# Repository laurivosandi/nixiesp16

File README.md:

# NixiESP16

Yet another Nixie clock project!

Some highlights:

* HV5530, HV5522 or similar driven IN-16 tubes
* CD4504B for 3.3V to 12V level shifting
* ESP8266 for time synchronization
* LM1117-3.3V for logic power supply
* No step up converter on-board, pin headers for connecting third party power supply
  <a href="http://www.ebay.com/itm/DC-5V-12V-to-170V-DC-High-Voltage-NIXIE-Power-Supply-Module-PSU-NIXIE-TUBE-ERA-/322511957768?hash=item4b1735ef08">third party power supply</a>
* HV5530 symbol created using
  <a href="http://kicad.rohrbacher.net/quicklib.php">Quick KICAD Library Component Builder</a>

Some KiCad screenshots:

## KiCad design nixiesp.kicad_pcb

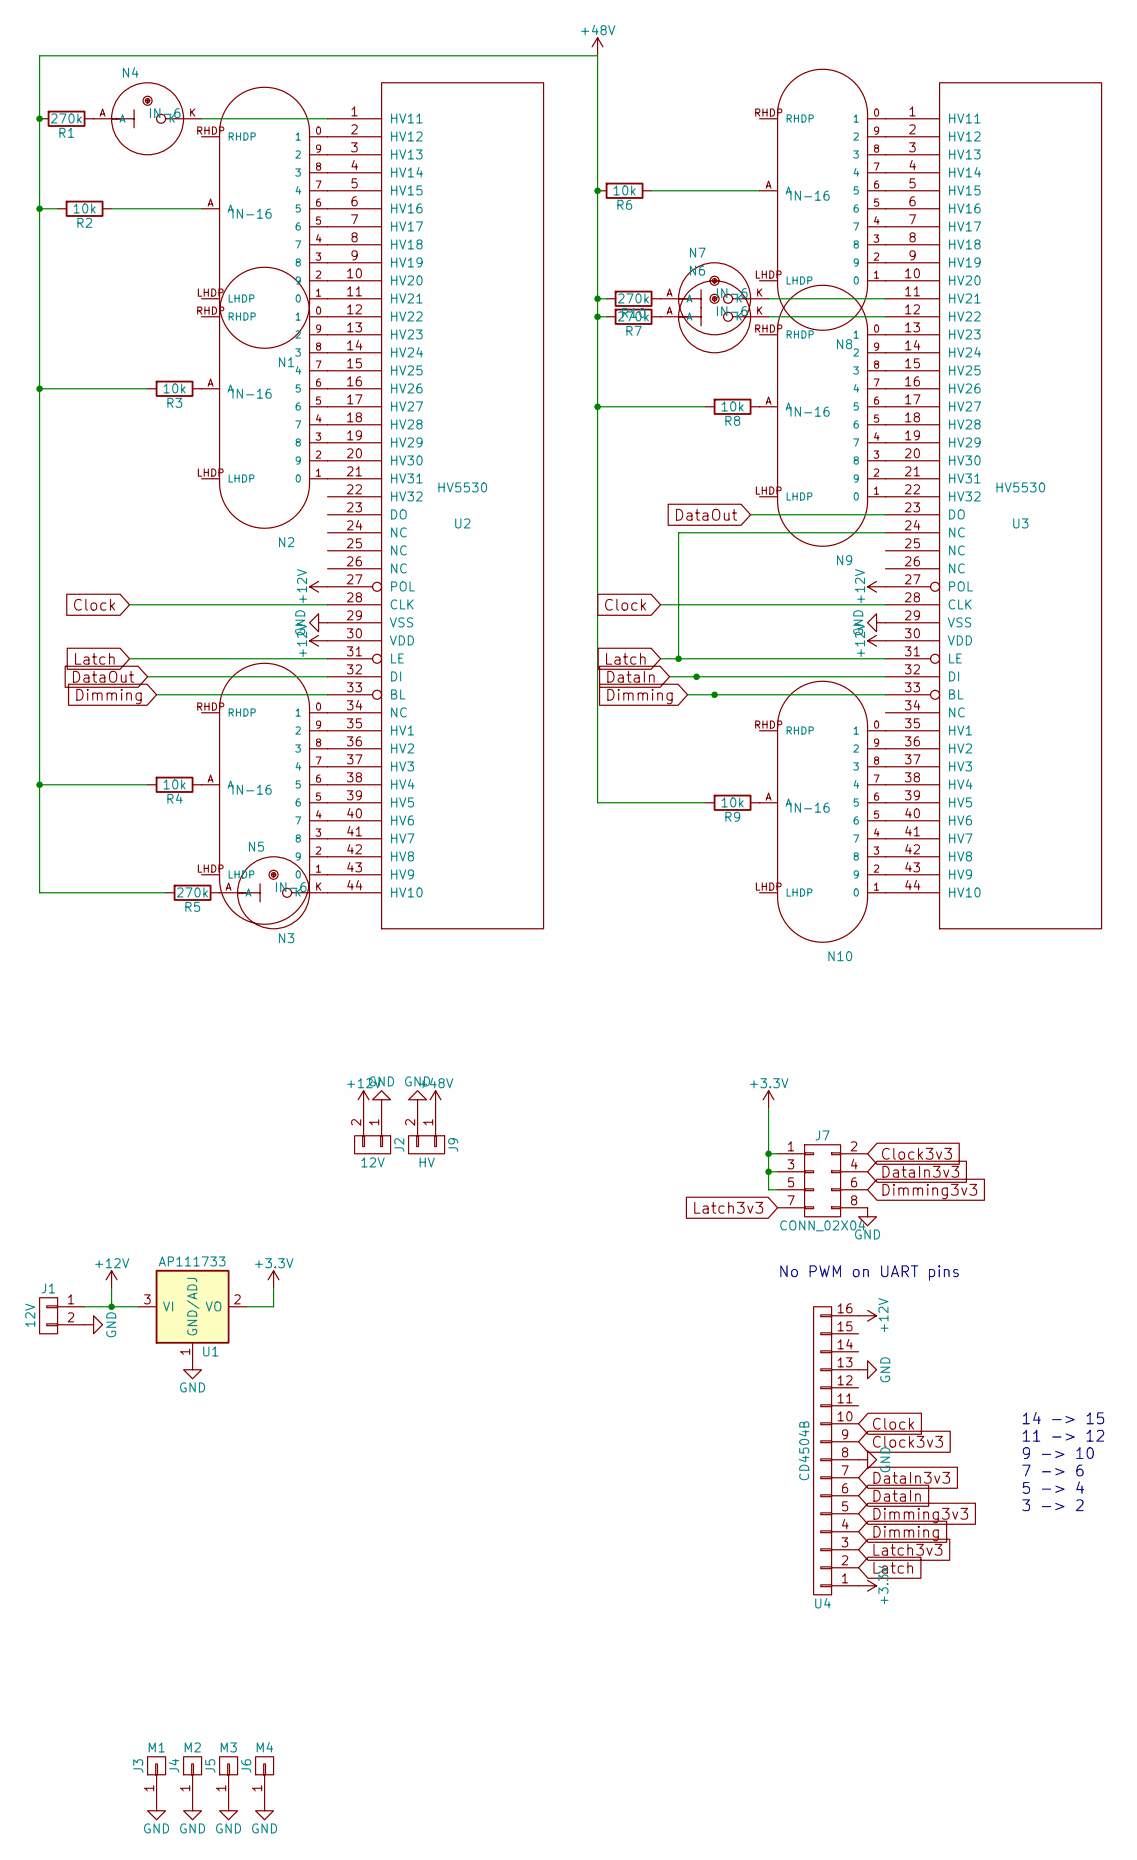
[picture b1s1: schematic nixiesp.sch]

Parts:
J1: 12V; TerminalBlock_Pheonix_PT-3.5mm_2pol
J2: 12V; Socket_Strip_Straight_1x02_Pitch2.54mm
J3: M1; 1pin
J4: M2; 1pin
J5: M3; 1pin
J6: M4; 1pin
J7: CONN_02X04; Socket_Strip_Straight_2x04_Pitch2.54mm
J9: HV; Socket_Strip_Straight_1x02_Pitch2.54mm
N1, N2, N3, N8, N9, N10: IN-16; russian-nixies-IN-16
N4, N5, N6, N7: IN-6; russian-nixies-IN-6
R1, R5, R7, R10: 270k; R_Axial_DIN0204_L3.6mm_D1.6mm_P2.54mm_Vertical
R2, R3, R4, R6, R8, R9: 10k; R_Axial_DIN0204_L3.6mm_D1.6mm_P2.54mm_Vertical
U1: AP111733; SOT-223
U2, U3: HV5530; PQFP-44_10x10mm_Pitch0.8mm
U4: CD4504B; SOIC-16_3.9x9.9mm_Pitch1.27mm

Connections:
+3V3: J7.1, J7.3, J7.5, U1.2 (VO), U1.4 (VO), U4.1
+12V: J1.1, J2.2, U1.3 (VI), U2.27 (POL), U2.30 (VDD), U3.27 (POL), U3.30 (VDD), U4.16
+48V: J9.1, R1.2, R2.2, R3.2, R4.2, R5.2, R6.2, R7.2, R8.2, R9.2, R10.2
Clock: U2.28 (CLK), U3.28 (CLK), U4.10
Clock3v3: J7.2, U4.9
DataIn: U3.32 (DI), U4.6
DataIn3v3: J7.4, U4.7
DataOut: U2.32 (DI), U3.23 (DO)
Dimming: U2.33 (BL), U3.33 (BL), U4.4
Dimming3v3: J7.6, U4.5
GND: J1.2, J2.1, J3.1, J4.1, J5.1, J6.1, J7.8, J9.2, U1.1 (GND/ADJ), U2.29 (VSS), U3.29 (VSS), U4.8, U4.13
Latch: U2.31 (LE), U3.24 (NC), U3.31 (LE), U4.2
Latch3v3: J7.7, U4.3
unnamed: N1.0 (1), U2.2 (HV12)
unnamed: N1.1 (0), U2.11 (HV21)
unnamed: N1.2 (9), U2.10 (HV20)
unnamed: N1.3 (8), U2.9 (HV19)
unnamed: N1.4 (7), U2.8 (HV18)
unnamed: N1.5 (6), U2.7 (HV17)
unnamed: N1.6 (5), U2.6 (HV16)
unnamed: N1.7 (4), U2.5 (HV15)
unnamed: N1.8 (3), U2.4 (HV14)
unnamed: N1.9 (2), U2.3 (HV13)
unnamed: N1.A, R2.1
unnamed: N2.0 (1), U2.12 (HV22)
unnamed: N2.1 (0), U2.21 (HV31)
unnamed: N2.2 (9), U2.20 (HV30)
unnamed: N2.3 (8), U2.19 (HV29)
unnamed: N2.4 (7), U2.18 (HV28)
unnamed: N2.5 (6), U2.17 (HV27)
unnamed: N2.6 (5), U2.16 (HV26)
unnamed: N2.7 (4), U2.15 (HV25)
unnamed: N2.8 (3), U2.14 (HV24)
unnamed: N2.9 (2), U2.13 (HV23)
unnamed: N2.A, R3.1
unnamed: N3.0 (1), U2.34 (NC)
unnamed: N3.1 (0), U2.43 (HV9)
unnamed: N3.2 (9), U2.42 (HV8)
unnamed: N3.3 (8), U2.41 (HV7)
unnamed: N3.4 (7), U2.40 (HV6)
unnamed: N3.5 (6), U2.39 (HV5)
unnamed: N3.6 (5), U2.38 (HV4)
unnamed: N3.7 (4), U2.37 (HV3)
unnamed: N3.8 (3), U2.36 (HV2)
unnamed: N3.9 (2), U2.35 (HV1)
unnamed: N3.A, R4.1
unnamed: N4.A, R1.1
unnamed: N4.K, U2.1 (HV11)
unnamed: N5.A, R5.1
unnamed: N5.K, U2.44 (HV10)
unnamed: N6.A, R7.1
unnamed: N6.K, U3.12 (HV22)
unnamed: N7.A, R10.1
unnamed: N7.K, U3.11 (HV21)
unnamed: N8.0 (1), U3.1 (HV11)
unnamed: N8.1 (0), U3.10 (HV20)
unnamed: N8.2 (9), U3.9 (HV19)
unnamed: N8.3 (8), U3.8 (HV18)
unnamed: N8.4 (7), U3.7 (HV17)
unnamed: N8.5 (6), U3.6 (HV16)
unnamed: N8.6 (5), U3.5 (HV15)
unnamed: N8.7 (4), U3.4 (HV14)
unnamed: N8.8 (3), U3.3 (HV13)
unnamed: N8.9 (2), U3.2 (HV12)
unnamed: N8.A, R6.1
unnamed: N9.0 (1), U3.13 (HV23)
unnamed: N9.1 (0), U3.22 (HV32)
unnamed: N9.2 (9), U3.21 (HV31)
unnamed: N9.3 (8), U3.20 (HV30)
unnamed: N9.4 (7), U3.19 (HV29)
unnamed: N9.5 (6), U3.18 (HV28)
unnamed: N9.6 (5), U3.17 (HV27)
unnamed: N9.7 (4), U3.16 (HV26)
unnamed: N9.8 (3), U3.15 (HV25)
unnamed: N9.9 (2), U3.14 (HV24)
unnamed: N9.A, R8.1
unnamed: N10.0 (1), U3.35 (HV1)
unnamed: N10.1 (0), U3.44 (HV10)
unnamed: N10.2 (9), U3.43 (HV9)
unnamed: N10.3 (8), U3.42 (HV8)
unnamed: N10.4 (7), U3.41 (HV7)
unnamed: N10.5 (6), U3.40 (HV6)
unnamed: N10.6 (5), U3.39 (HV5)
unnamed: N10.7 (4), U3.38 (HV4)
unnamed: N10.8 (3), U3.37 (HV3)
unnamed: N10.9 (2), U3.36 (HV2)
unnamed: N10.A, R9.1

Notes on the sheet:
No PWM on UART pins
14 -> 15 11 -> 12 9 -> 10 7 -> 6 5 -> 4 3 -> 2

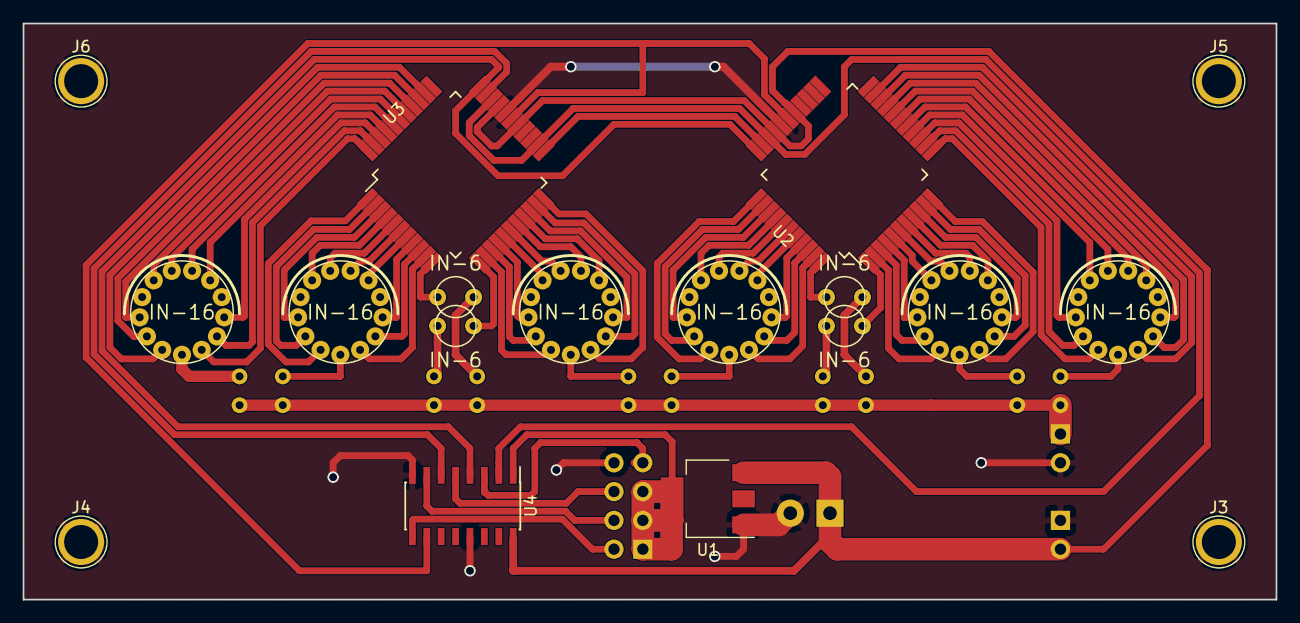
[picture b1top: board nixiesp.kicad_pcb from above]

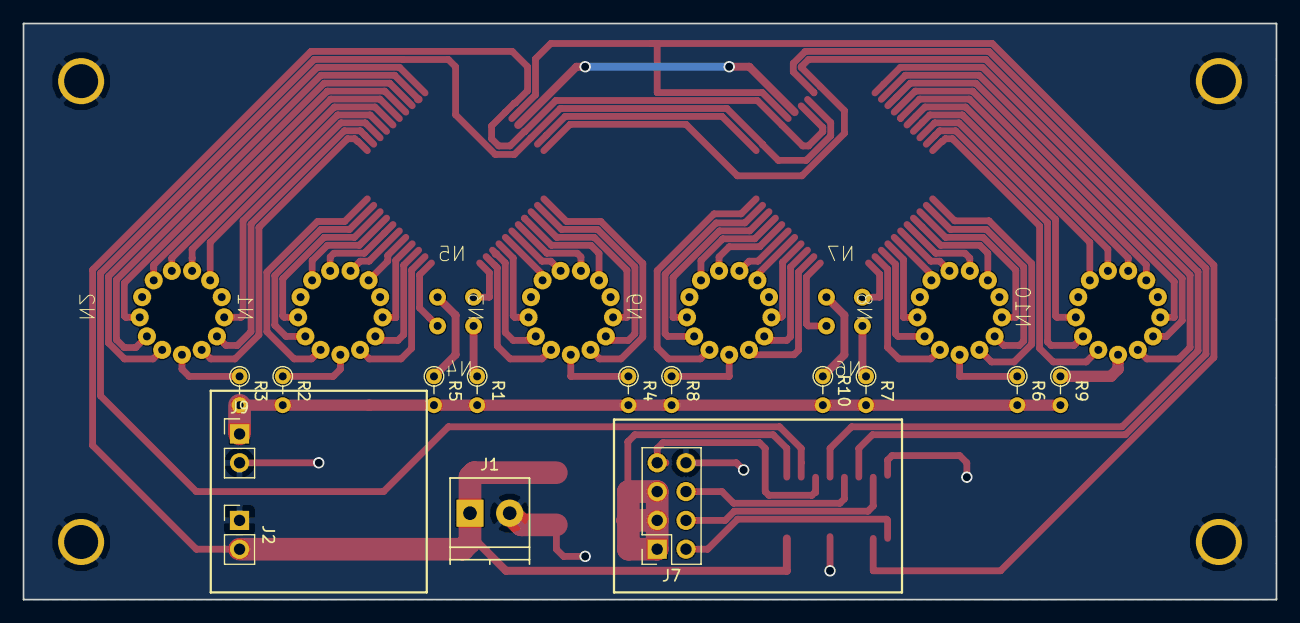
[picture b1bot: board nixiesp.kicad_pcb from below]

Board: 2 copper layers, 110.5 x 50.8 mm, 32 parts (14 on the bottom side), 87 nets.
